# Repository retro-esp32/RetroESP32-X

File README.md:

# Introducing the Retro ESP32 *X*

> Gameboy Pocket Drop In PCB

We're thrilled to unveil the latest and greatest iteration of our beloved Retro ESP32 - the Retro ESP32 X! 🚀🕹️

**Retro ESP32 X** is certified unde Open Source Hardware as OSHWA UID [CA000030](https://certification.oshwa.org/ca000030.html) with CC-BY-SA-4.0 licensing

## What's Public

- [x] PCB
- [x] Schematic
- [x] BOM
- [x] Gerber
- [x] DXF

## Updated Features

- [x] 2.6" ILI9342C SPI ISP
- [x] FPC Ribbon Connector
- [x] USB C (Charge Only)
- [x] Serial Pin Breakout

## Images

|     |      |
| ---- | ------ |
| Top  | Bottom |

## Authors

* **Eugene Yevhen Andruszczenko** - *Initial and Ongoing Work* - [32teeth](https://github.com/32teeth)

### License

This project is licensed under the Creative Commons Attribution Share Alike 4.0 International - see the [LICENSE.md](LICENSE.md) file for details

## Support
> Although we do this for 💕 of 🕹️<br/>
> **We Also Like Coffee!** <br/>
> *Please Consider Supporting* <br/>

Did you know, you can support us in a few way? We offer multiple sposorship tiers, with different rewards!

Take a *look*.
See what *fits*.

**Thank You**

-----

**📢 Important Update:**
Please note that the original Retro ESP32 is now deprecated and is no longer supported. But fret not, because the all-new Retro ESP32 X is here to take your gaming experience to new heights! 📈✨

***The Retro ESP32 X uses the firmware from [Ducalex - Retro Go](https://github.com/ducalex/retro-go)***

Link to the Origina Rettro ESP32 Firmware Repo: [Check it out here!](https://github.com/retro-esp32/RetroESP32)

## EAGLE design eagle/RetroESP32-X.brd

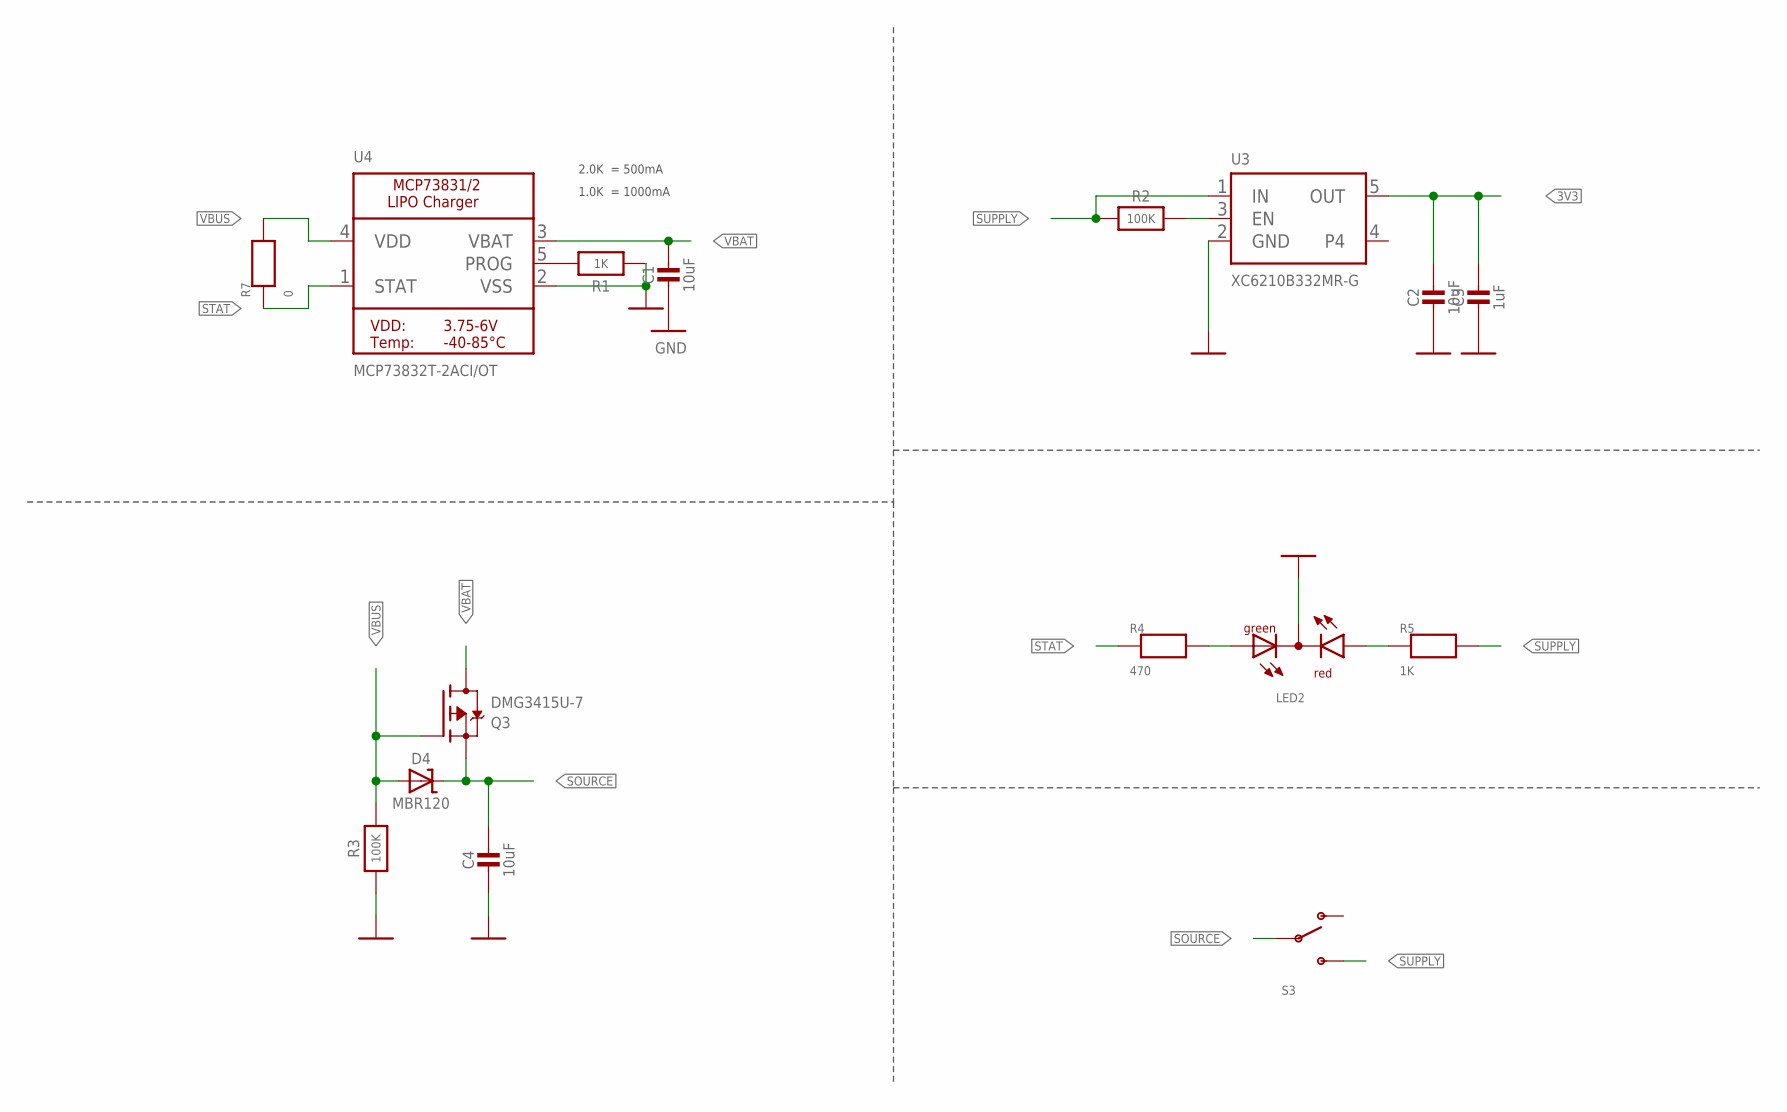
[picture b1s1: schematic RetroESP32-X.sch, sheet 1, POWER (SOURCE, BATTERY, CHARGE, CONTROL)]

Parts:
C1, C2, C4: 10uF; 0603-MINI-CAP; MPN CL10A106MP8NNNC
C3: 1uF; 0603-MINI-CAP; MPN CL10A105KP8NNNC
D4: MBR120; SOD-123; MPN MBR120LSFT1G
LED2: LED_L-115WEGW-CA; LED_DUOLED-A-3MM; MPN SSL-LX3059IGW
Q3: DMG3415U-7; SOT23-R; MPN DMG3415U-7
R1, R5: 1K; 0603-MINI; MPN ERJ-PA3J102V
R2, R3: 100K; 0603-MINI; MPN ERJ-PA3J104V
R4: 470; 0603-MINI; MPN ERJ-PA3J471V
R7: 0; 0603-MINI; MPN ERJ-3GEY0R00V
S3: POWER-SWITCH; RETIRED_KPS-1290; MPN MA12RTR
U3: XC6210B332MR-G; SOT23-5; MPN XC6210B332MR-G
U4: MCP73832T-2ACI/OT; SOT23-5-1; MPN MCP73832T-2ACI/OT

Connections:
3V3: C2.1, C3.1, U3.5 (OUT); also elsewhere on the board
EN: R2.2, U3.3 (EN)
GND: C1.2, C2.2, C3.2, C4.2, LED2.2 (A), R1.1, R3.1, U3.2 (GND), U4.2 (VSS); also elsewhere on the board
POWER_LED: LED2.3 (CR), R5.1
PROG: R1.2, U4.5 (PROG)
SOURCE: C4.1, D4.C, Q3.2 (S), S3.P
STAT: R4.1, R7.1, U4.1 (STAT)
STAT_LED: LED2.1 (CG), R4.2
SUPPLY: R2.1, R5.2, S3.S, U3.1 (IN)
VBAT: C1.1, Q3.3 (D), U4.3 (VBAT); also elsewhere on the board
VBUS: D4.A, Q3.1 (G), R3.2, R7.2, U4.4 (VDD); also elsewhere on the board

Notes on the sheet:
2.0K = 500mA
1.0K = 1000mA

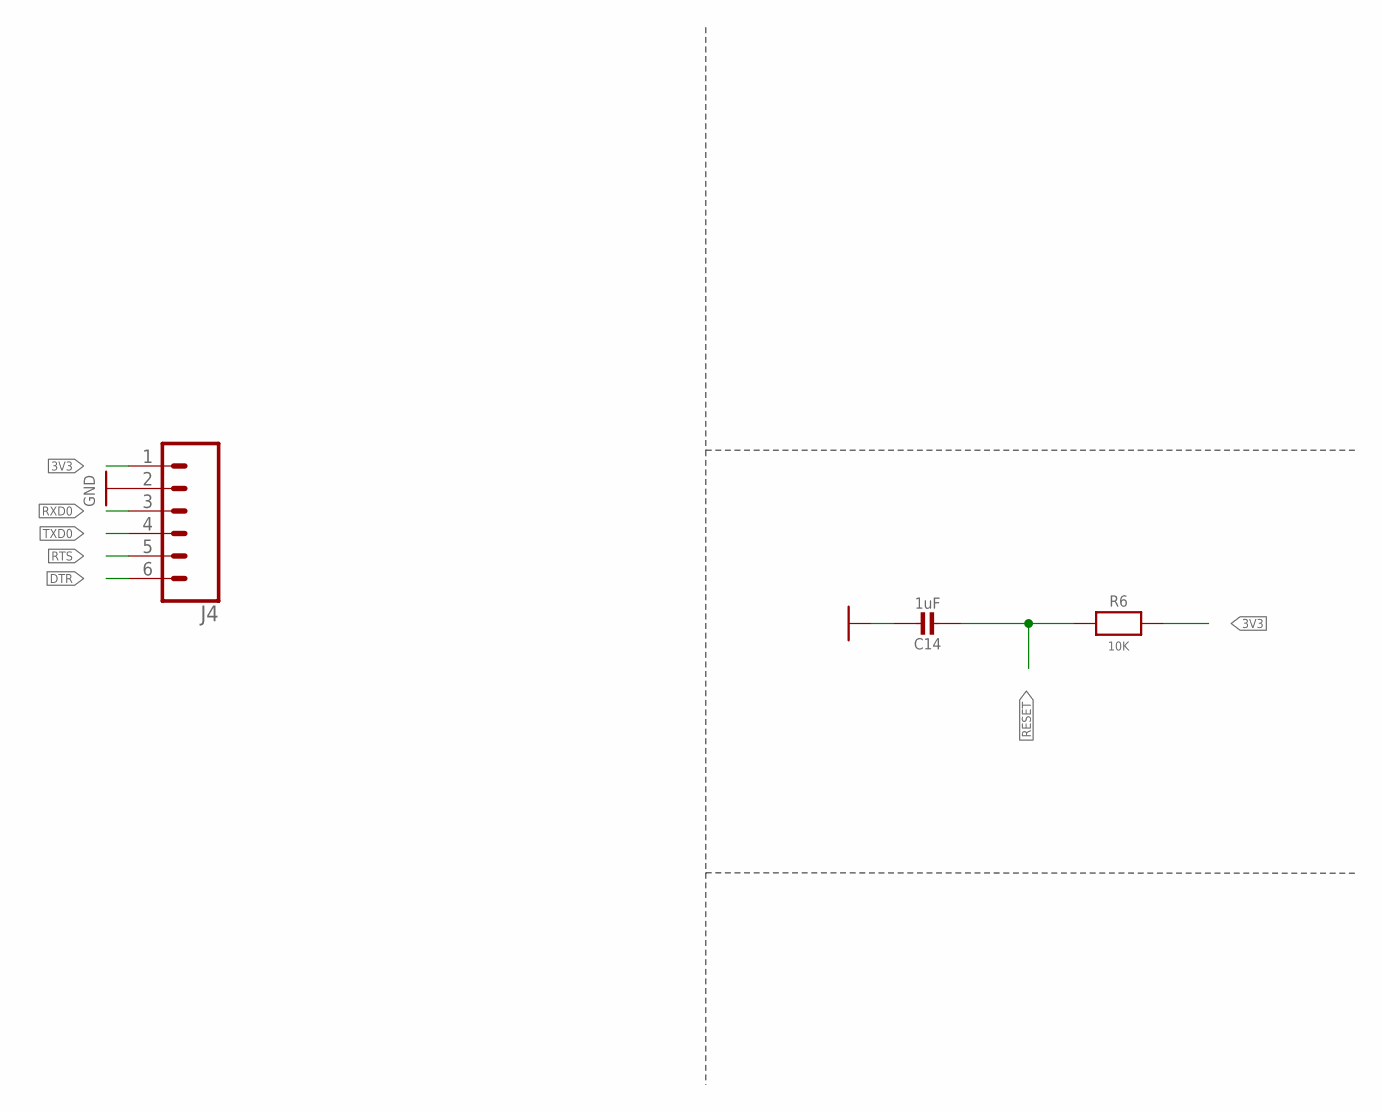
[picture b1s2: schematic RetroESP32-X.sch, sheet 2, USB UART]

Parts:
C14: 1uF; 0603-MINI-CAP; MPN CL10A105KP8NNNC
J4: CONN_06NO_SILK_NO_POP; 1X06_NO_SILK
R6: 10K; 0603-MINI; MPN ERJ-PA3J103V

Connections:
3V3: J4.1, R6.2; also elsewhere on the board
DTR: J4.6; also elsewhere on the board
GND: C14.1, J4.2; also elsewhere on the board
RESET: C14.2, R6.1; also elsewhere on the board
RTS: J4.5; also elsewhere on the board
RXD0: J4.3; also elsewhere on the board
TXD0: J4.4; also elsewhere on the board

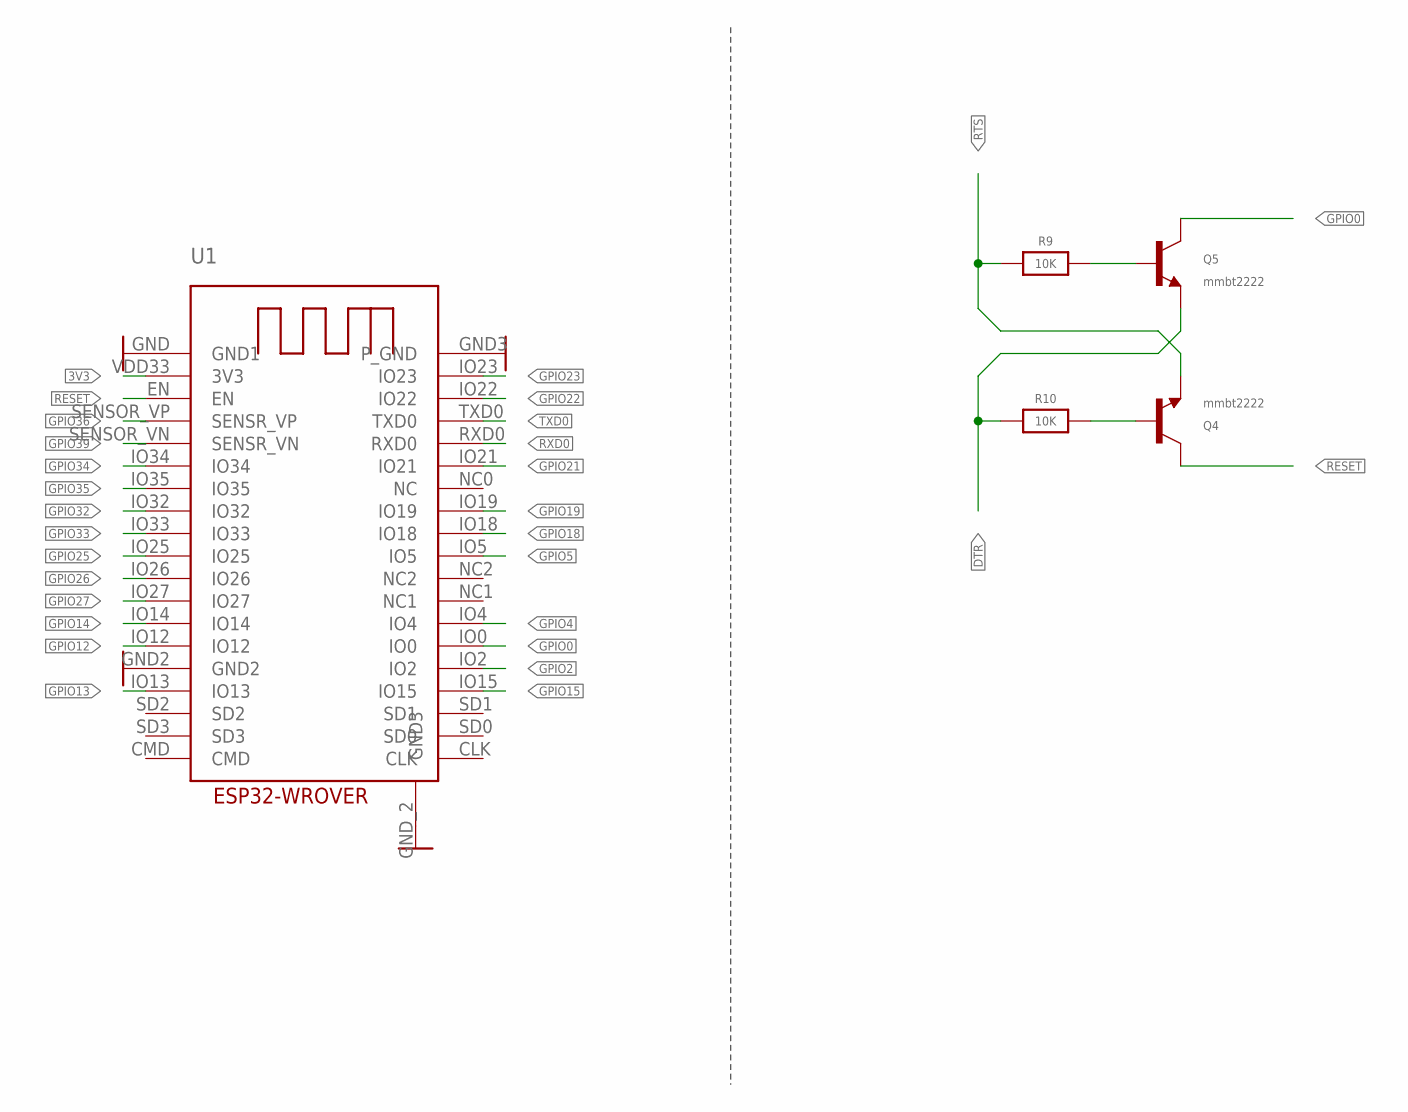
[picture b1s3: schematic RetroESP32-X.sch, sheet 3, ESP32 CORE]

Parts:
Q4, Q5: mmbt2222; SOT23-3; MPN MMBT2222A-7-F
R9, R10: 10K; 0603-MINI; MPN ERJ-PA3J103V
U1: ESP32-WROVER; ESP32-WROVER_ESP32-WROVER; MPN ESP32-WROVER (16MB)

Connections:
3V3: U1.VDD33 (3V3); also elsewhere on the board
DTR: Q5.2 (E), R10.1; also elsewhere on the board
GND: U1.GND (GND1), U1.GND2, U1.GND3 (P_GND), U1.GND_2 (GND3); also elsewhere on the board
GPIO0: Q5.3 (C), U1.IO0
GPIO2: U1.IO2
GPIO4: U1.IO4
GPIO5: U1.IO5; also elsewhere on the board
GPIO12: U1.IO12
GPIO13: U1.IO13
GPIO14: U1.IO14
GPIO15: U1.IO15
GPIO18: U1.IO18; also elsewhere on the board
GPIO19: U1.IO19; also elsewhere on the board
GPIO21: U1.IO21; also elsewhere on the board
GPIO22: U1.IO22; also elsewhere on the board
GPIO23: U1.IO23; also elsewhere on the board
GPIO25: U1.IO25
GPIO26: U1.IO26; also elsewhere on the board
GPIO27: U1.IO27; also elsewhere on the board
GPIO32: U1.IO32; also elsewhere on the board
GPIO33: U1.IO33; also elsewhere on the board
GPIO34: U1.IO34; also elsewhere on the board
GPIO35: U1.IO35; also elsewhere on the board
GPIO36: U1.SENSOR_VP (SENSR_VP); also elsewhere on the board
GPIO39: U1.SENSOR_VN (SENSR_VN); also elsewhere on the board
RESET: Q4.3 (C), U1.EN; also elsewhere on the board
RST-RES: Q4.1 (B), R10.2
RTS: Q4.2 (E), R9.1; also elsewhere on the board
RTS-RES: Q5.1 (B), R9.2
RXD0: U1.RXD0; also elsewhere on the board
TXD0: U1.TXD0; also elsewhere on the board

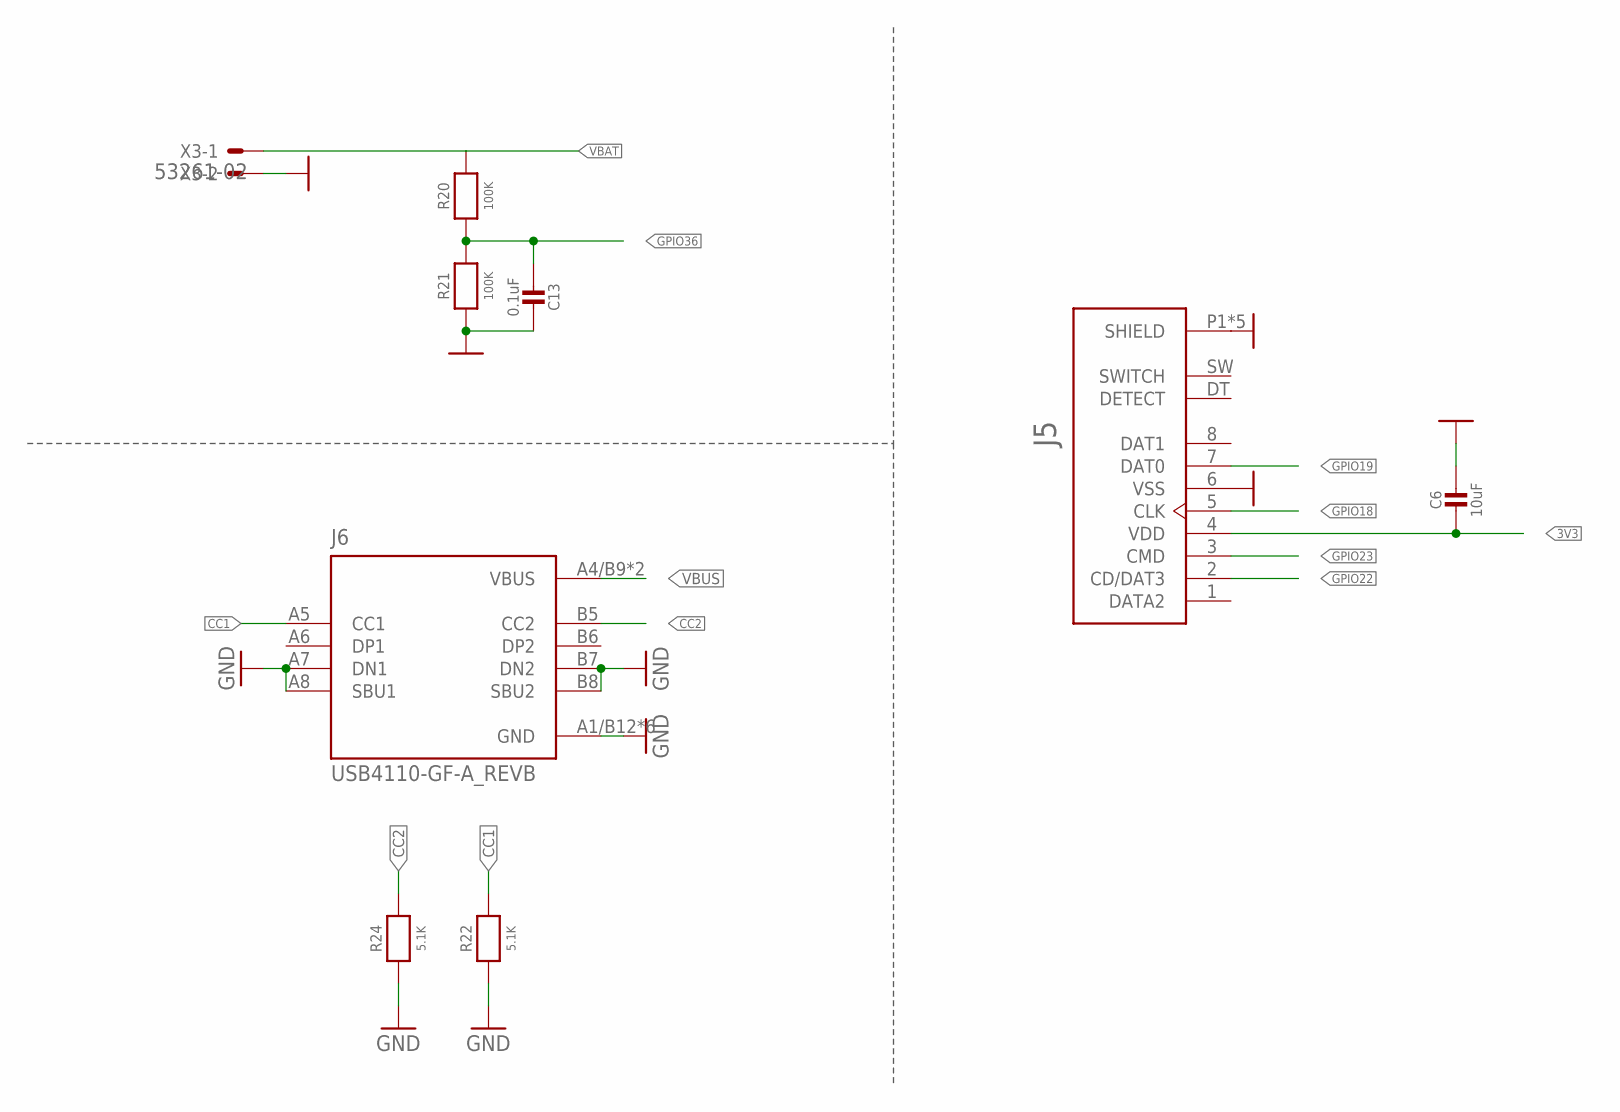
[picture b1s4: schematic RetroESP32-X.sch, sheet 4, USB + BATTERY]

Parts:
C6: 10uF; 0603-MINI-CAP; MPN CL10A106MP8NNNC
C13: 0.1uF; 0603-MINI-CAP; MPN CL10B104KB8NNNC
J5: 503182-1852_503182-1852; 503182-1852_MOLEX_503182-1852; MPN 5031821852
J6: USB4110-GF-A_REVB; GCT_USB4110-GF-A_REVB; MPN USB4105-GF-A
R20, R21: 100K; 0603-MINI; MPN ERJ-PA3J104V
R22, R24: 5.1K; 0603-MINI; MPN ERJ-PA3F5101V
X3: 53261-02; MPN 0532614002

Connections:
3V3: C6.2, J5.4 (VDD); also elsewhere on the board
CC1: J6.A5 (CC1), R22.2
CC2: J6.B5 (CC2), R24.2
GND: C6.1, C13.1, J5.6 (VSS), J5.P1 (SHIELD), J5.P2 (SHIELD), J5.P3 (SHIELD), J5.P4 (SHIELD), J5.P5 (SHIELD), J6.A1/B12 (GND), J6.A7 (DN1), J6.A8 (SBU1), J6.B1/A12 (GND), J6.B7 (DN2), J6.B8 (SBU2), J6.S1 (GND), J6.S2 (GND), J6.S3 (GND), J6.S4 (GND), R21.1, R22.1, R24.1, X3.2; also elsewhere on the board
GPIO18: J5.5 (CLK); also elsewhere on the board
GPIO19: J5.7 (DAT0); also elsewhere on the board
GPIO22: J5.2 (CD/DAT3); also elsewhere on the board
GPIO23: J5.3 (CMD); also elsewhere on the board
GPIO36: C13.2, R20.1, R21.2; also elsewhere on the board
VBAT: R20.2, X3.1; also elsewhere on the board
VBUS: J6.A4/B9 (VBUS), J6.B4/A9 (VBUS); also elsewhere on the board

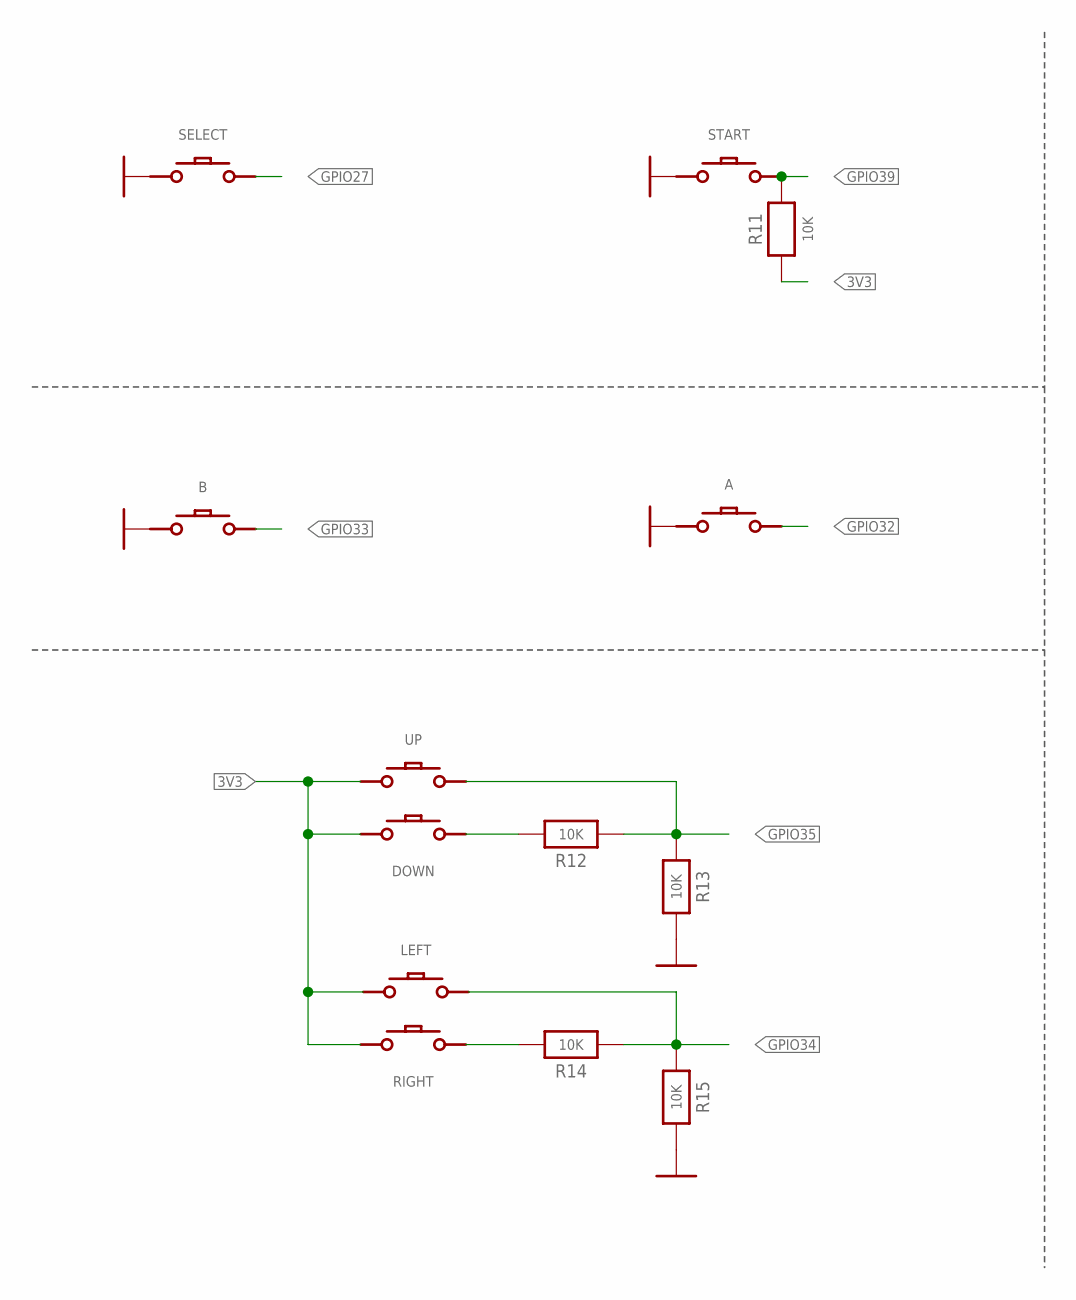
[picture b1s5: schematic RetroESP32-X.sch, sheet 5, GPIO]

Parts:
A: BUTTONSCONDUCTIVE_BUTTON_MGB; ACTION-GAMEBOY
B: BUTTONSCONDUCTIVE_BUTTON_MGB; ACTION-GAMEBOY
DOWN: BUTTONSCONDUCTIVE_BUTTON_DIRECTION_THIN; DIRECTIONAL-SPACED-PAD
LEFT: BUTTONSCONDUCTIVE_BUTTON_DIRECTION_THIN; DIRECTIONAL-SPACED-PAD
R11, R12, R13, R14, R15: 10K; 0603-MINI; MPN ERJ-PA3J103V
RIGHT: BUTTONSCONDUCTIVE_BUTTON_DIRECTION_THIN; DIRECTIONAL-SPACED-PAD
SELECT: BUTTON_START+SELECT; START+SELECT-STANDARD
START: BUTTON_START+SELECT; START+SELECT-STANDARD
UP: BUTTONSCONDUCTIVE_BUTTON_DIRECTION_THIN; DIRECTIONAL-SPACED-PAD

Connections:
3V3: DOWN.P$GND, LEFT.P$GND, R11.1, RIGHT.P$GND, UP.P$GND; also elsewhere on the board
DOWN: DOWN.P$ACTIVE, R12.2
GND: A.P$GND, A.P$GND1 (P$GND), B.P$GND, B.P$GND1 (P$GND), R13.2, R15.2, SELECT.P$GND, SELECT.P$GND1 (P$GND), SELECT.P$GND2 (P$GND), SELECT.P$GND3 (P$GND), START.P$GND, START.P$GND1 (P$GND), START.P$GND2 (P$GND), START.P$GND3 (P$GND); also elsewhere on the board
GPIO27: SELECT.P$ACTIVE, SELECT.P$ACTIVE1 (P$ACTIVE), SELECT.P$ACTIVE2 (P$ACTIVE), SELECT.P$ACTIVE3 (P$ACTIVE), SELECT.P$ACTIVE4 (P$ACTIVE), SELECT.P$ACTIVE5 (P$ACTIVE), SELECT.P$ACTIVE6 (P$ACTIVE); also elsewhere on the board
GPIO32: A.P$ACTIVE, A.P$ACTIVE1 (P$ACTIVE); also elsewhere on the board
GPIO33: B.P$ACTIVE, B.P$ACTIVE1 (P$ACTIVE); also elsewhere on the board
GPIO34: LEFT.P$ACTIVE, R14.1, R15.1; also elsewhere on the board
GPIO35: R12.1, R13.1, UP.P$ACTIVE; also elsewhere on the board
GPIO39: R11.2, START.P$ACTIVE, START.P$ACTIVE1 (P$ACTIVE), START.P$ACTIVE2 (P$ACTIVE), START.P$ACTIVE3 (P$ACTIVE), START.P$ACTIVE4 (P$ACTIVE), START.P$ACTIVE5 (P$ACTIVE), START.P$ACTIVE6 (P$ACTIVE); also elsewhere on the board
RIGHT: R14.2, RIGHT.P$ACTIVE

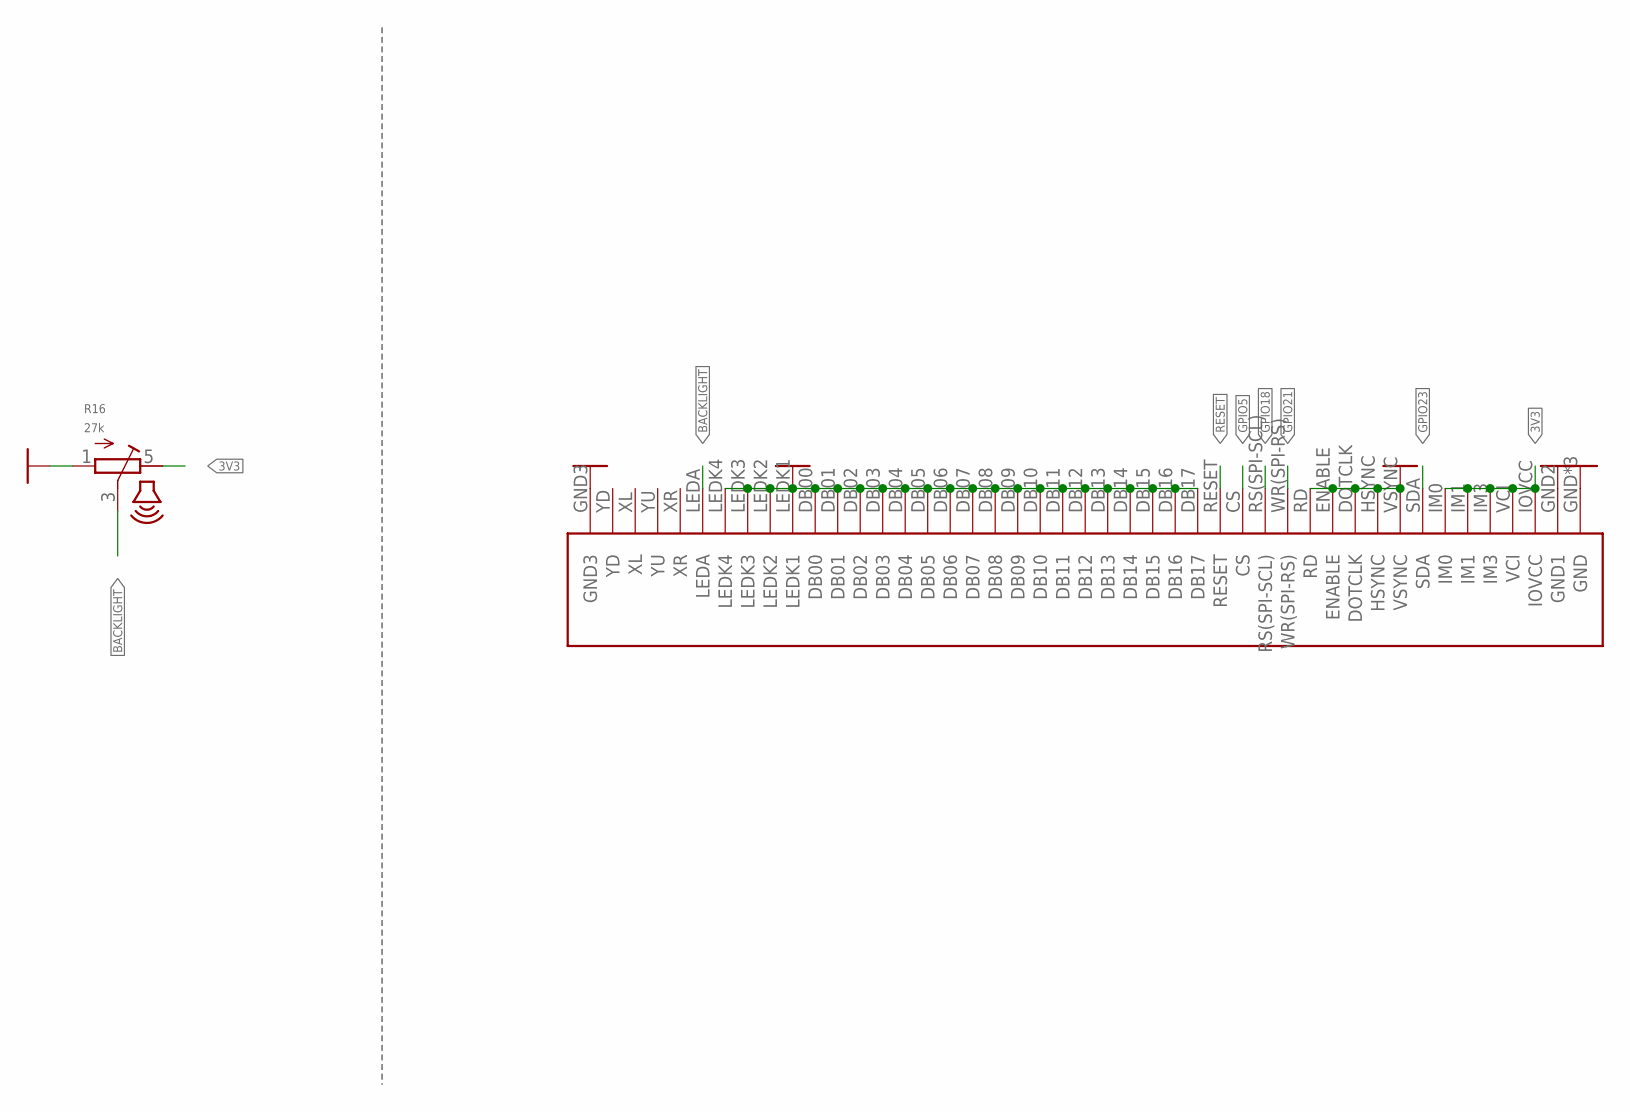
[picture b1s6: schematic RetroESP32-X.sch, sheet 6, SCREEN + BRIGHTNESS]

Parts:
R16: 27k; THUMBWHEEL
U$11: LCD-ILI9342CKD026LQTMA008=PASSTHRU-2023; KD026LQTMA008-PASSTHRU-2023; MPN 0541044531

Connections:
3V3: R16.5 (E), U$11.IM0, U$11.IM1, U$11.IM3, U$11.IOVCC, U$11.VCI; also elsewhere on the board
BACKLIGHT: R16.3 (S), U$11.LEDA
GND: R16.1 (A), U$11.DB00, U$11.DB01, U$11.DB02, U$11.DB03, U$11.DB04, U$11.DB05, U$11.DB06, U$11.DB07, U$11.DB08, U$11.DB09, U$11.DB10, U$11.DB11, U$11.DB12, U$11.DB13, U$11.DB14, U$11.DB15, U$11.DB16, U$11.DB17, U$11.DOTCLK, U$11.ENABLE, U$11.GND, U$11.GND2 (GND1), U$11.GND3, U$11.HSYNC, U$11.LEDK1, U$11.LEDK2, U$11.LEDK3, U$11.LEDK4, U$11.PAD$1 (GND), U$11.PAD$2 (GND), U$11.RD, U$11.VSYNC; also elsewhere on the board
GPIO5: U$11.CS; also elsewhere on the board
GPIO18: U$11.RS(SPI-SCL); also elsewhere on the board
GPIO21: U$11.WR(SPI-RS); also elsewhere on the board
GPIO23: U$11.SDA; also elsewhere on the board
RESET: U$11.RESET; also elsewhere on the board

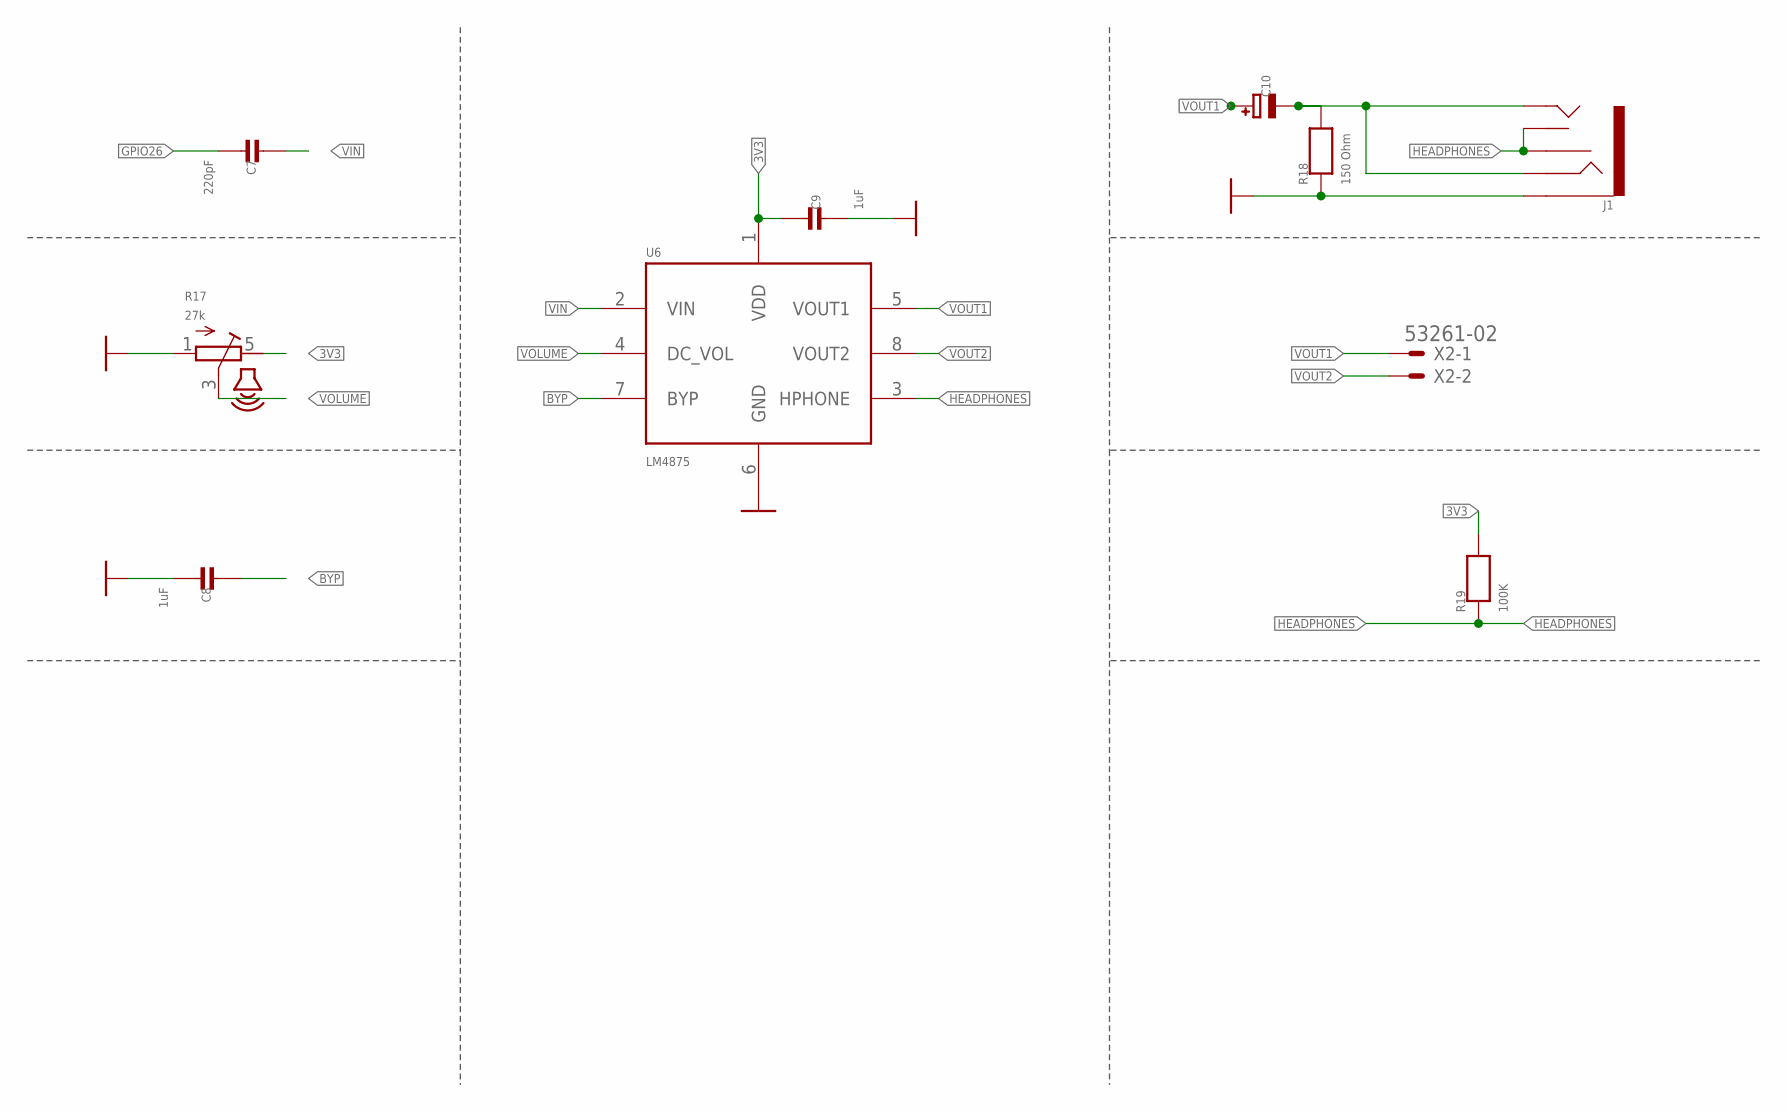
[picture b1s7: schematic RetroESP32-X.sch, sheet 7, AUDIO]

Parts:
C7: 220pF; 0603-MINI-CAP; MPN CL10C221JB8NNNC
C8, C9: 1uF; 0603-MINI-CAP; MPN CL10A105KP8NNNC
C10: 100uF; EIA3216-18/A-W; MPN F930J107KAA
J1: AUDIO_JACK_3.5MM_KIT; AUDIO-JACK-KIT; MPN SJ1-3525NG-GR
R17: 27k; THUMBWHEEL
R18: 150 Ohm; 0603-MINI; MPN ERJ-PA3J151V
R19: 100K; 0603-MINI; MPN ERJ-PA3J104V
U6: LM4875; SOIC8; MPN LM4875MX/NOPB
X2: 53261-02; MPN 0532614002

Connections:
3V3: C9.1, R17.5 (E), R19.2, U6.1 (VDD); also elsewhere on the board
BYP: C8.1, U6.7 (BYP)
GND: C8.2, C9.2, J1.SLEEVE, R17.1 (A), R18.1, U6.6 (GND); also elsewhere on the board
GPIO26: C7.2; also elsewhere on the board
HEADPHONES: J1.RSH, J1.TSH, R19.1, U6.3 (HPHONE)
VIN: C7.1, U6.2 (VIN)
VIN1: C10.-, J1.RING, J1.TIP, R18.2
VOLUME: R17.3 (S), U6.4 (DC_VOL)
VOUT1: C10.+, U6.5 (VOUT1), X2.1
VOUT2: U6.8 (VOUT2), X2.2

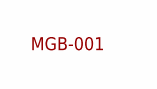
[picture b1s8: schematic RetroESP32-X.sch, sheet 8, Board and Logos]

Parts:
U$17: POCKET-BOARDSMGB-001-ESP32-2023; MGB-001-ESP32-2023

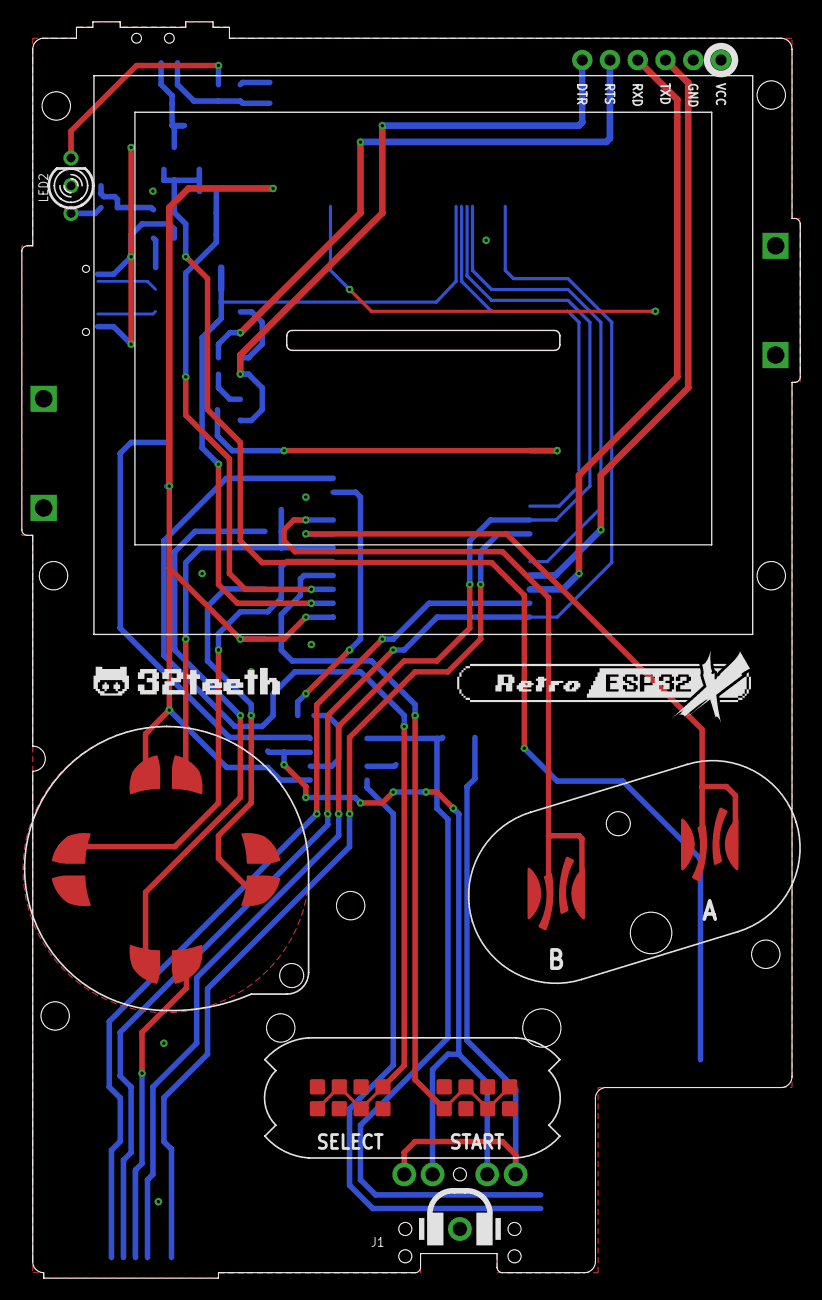
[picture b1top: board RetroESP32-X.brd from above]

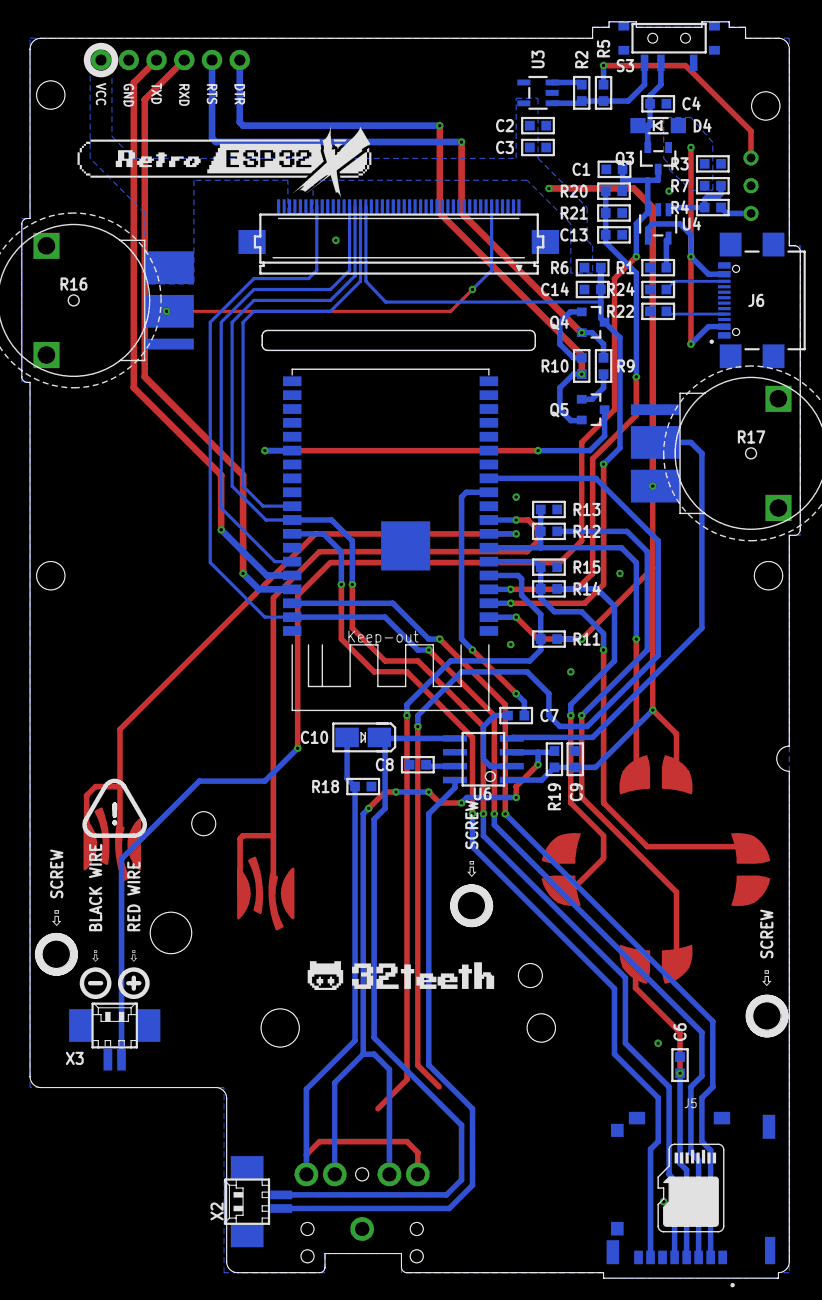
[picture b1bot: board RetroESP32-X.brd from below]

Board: 2 copper layers, 71.2 x 115.0 mm, 59 parts (46 on the bottom side), 45 nets.

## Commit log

2021-03-18 Thu 18 Mar 2021 09:27:54 EDT - Public Release
2021-03-18 Thu 18 Mar 2021 09:44:26 EDT - Public Release
2022-02-25 updated CC1/2 pins
2022-02-27 Added new DXF and BOM
2022-03-11 added resistors to USB
2022-11-23 updated BOM
2023-02-08 added potentiometer part number
2023-03-28 chore: pre indiegogo commit
2023-04-25 feat: new button library
2023-04-26 feat: new A/B buttons, osh gerber
2023-04-26 feat: new A/B buttons, osh gerber, pdf schema
2023-05-17 fix: restore brd files
2023-06-27 feat: update gerbers
2023-06-27 feat: updated U$11 component
2023-06-27 feat: updated gerbers
2023-06-29 feat: updated shim
2023-07-02 feat: new layout
2023-07-10 feat: replaced JST with molex connector
2023-07-10 feat: tighter d-pad
2023-07-10 feat: splash screen
2023-07-10 feat: new splash
2023-07-23 feat: released X
2023-08-01 feat: new board with passthrough lcd
2023-08-12 feature: updated BOM for X
2023-10-06 update: BOM for X
2023-10-29 Update: Tindie markdown update
2024-07-25 README.md

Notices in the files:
parts and their libraries:
SparkFun-Connectors: Licensing: Creative Commons ShareAlike 4.0 International - https://creativecommons.org/licenses/by-sa/4.0
